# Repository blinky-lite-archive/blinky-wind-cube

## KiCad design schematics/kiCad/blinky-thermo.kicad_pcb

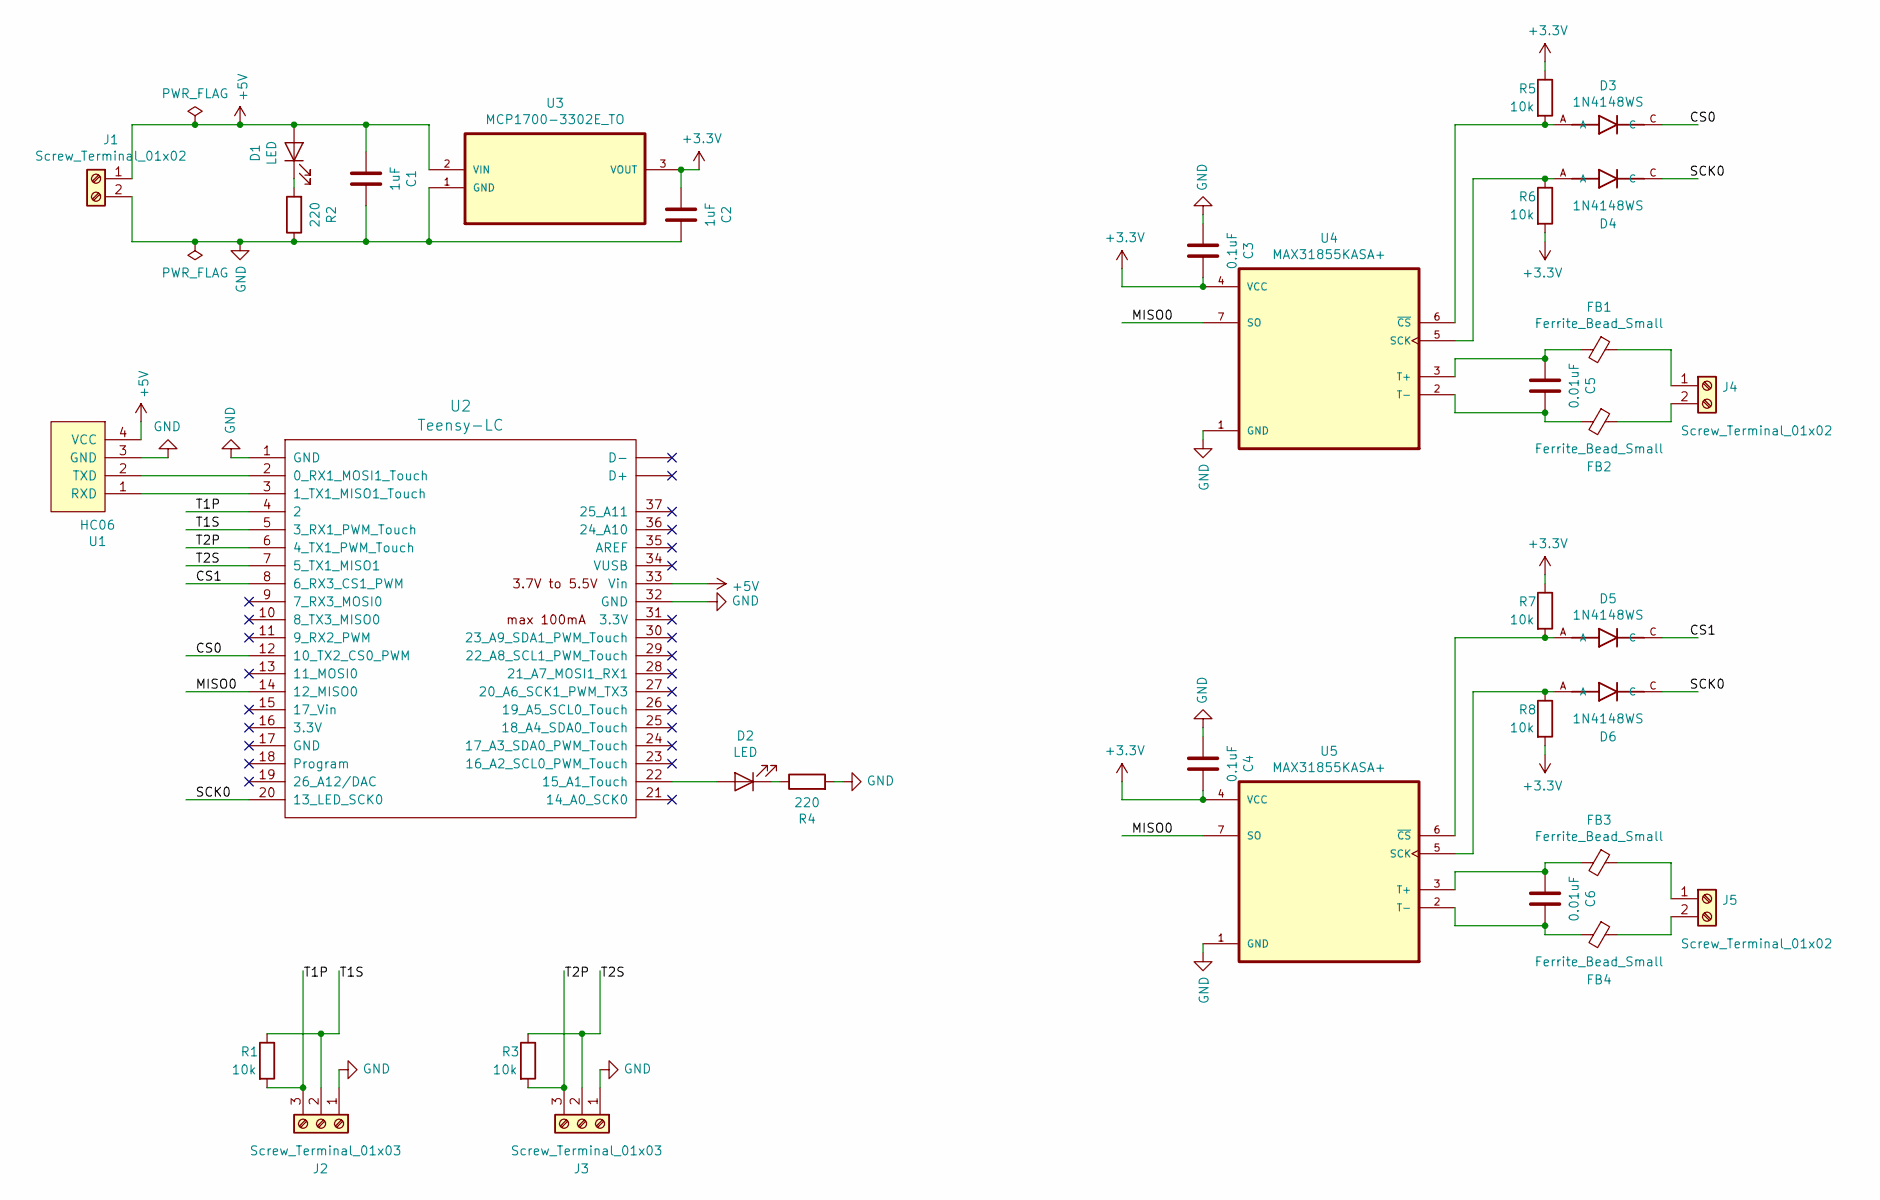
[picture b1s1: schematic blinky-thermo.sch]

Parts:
C1, C2: 1uF; C_1206_3216Metric_Pad1.42x1.75mm_HandSolder
C3, C4: 0.1uF; C_1206_3216Metric_Pad1.42x1.75mm_HandSolder
C5, C6: 0.01uF; C_1206_3216Metric_Pad1.42x1.75mm_HandSolder
D1, D2: LED; LED_D5.0mm
D3, D4, D5, D6: 1N4148WS; SODFL2512X100N
FB1, FB2, FB3, FB4: Ferrite_Bead_Small; L_1206_3216Metric_Pad1.42x1.75mm_HandSolder
J1, J4, J5: Screw_Terminal_01x02; TerminalBlock_bornier-2_P5.08mm
J2, J3: Screw_Terminal_01x03; TerminalBlock_bornier-3_P5.08mm
R1, R3, R5, R6, R7, R8: 10k; R_1206_3216Metric_Pad1.42x1.75mm_HandSolder
R2, R4: 220; R_1206_3216Metric_Pad1.42x1.75mm_HandSolder
U1: HC06
U2: Teensy-LC; Teensy30_31_32_LC
U3: MCP1700-3302E_TO; TO127P254X495-3; MPN MCP1700-3302E/TO
U4, U5: MAX31855KASA+; SOIC127P600X175-8N

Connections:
+3V3: C2.2, C3.1, C4.1, R5.1, R6.2, R7.1, R8.2, U3.3 (VOUT), U4.4 (VCC), U5.4 (VCC)
+5V: C1.2, D1.2 (A), J1.1, U1.4 (VCC), U2.33 (Vin), U3.2 (VIN)
/CS0: D3.C, U2.12 (10_TX2_CS0_PWM)
/CS1: D5.C, U2.8 (6_RX3_CS1_PWM)
/MISO0: U2.14 (12_MISO0), U4.7 (SO), U5.7 (SO)
/SCK0: D4.C, D6.C, U2.20 (13_LED_SCK0)
/T1P: J2.3, R1.2, U2.4 (2)
/T1S: J2.2, R1.1, U2.5 (3_RX1_PWM_Touch)
/T2P: J3.3, R3.2, U2.6 (4_TX1_PWM_Touch)
/T2S: J3.2, R3.1, U2.7 (5_TX1_MISO1)
GND: C1.1, C2.1, C3.2, C4.2, J1.2, J2.1, J3.1, R2.1, R4.2, U1.3 (GND), U2.1 (GND), U2.32 (GND), U3.1 (GND), U4.1 (GND), U5.1 (GND)
unnamed: C5.1, FB2.2, U4.2 (T-)
unnamed: C5.2, FB1.2, U4.3 (T+)
unnamed: C6.1, FB4.2, U5.2 (T-)
unnamed: C6.2, FB3.2, U5.3 (T+)
unnamed: D1.1 (K), R2.2
unnamed: D2.1 (K), R4.1
unnamed: D2.2 (A), U2.22 (15_A1_Touch)
unnamed: D3.A, R5.2, U4.6 (~CS)
unnamed: D4.A, R6.1, U4.5 (SCK)
unnamed: D5.A, R7.2, U5.6 (~CS)
unnamed: D6.A, R8.1, U5.5 (SCK)
unnamed: FB1.1, J4.1
unnamed: FB2.1, J4.2
unnamed: FB3.1, J5.1
unnamed: FB4.1, J5.2
unnamed: U1.1 (RXD), U2.3 (1_TX1_MISO1_Touch)
unnamed: U1.2 (TXD), U2.2 (0_RX1_MOSI1_Touch)

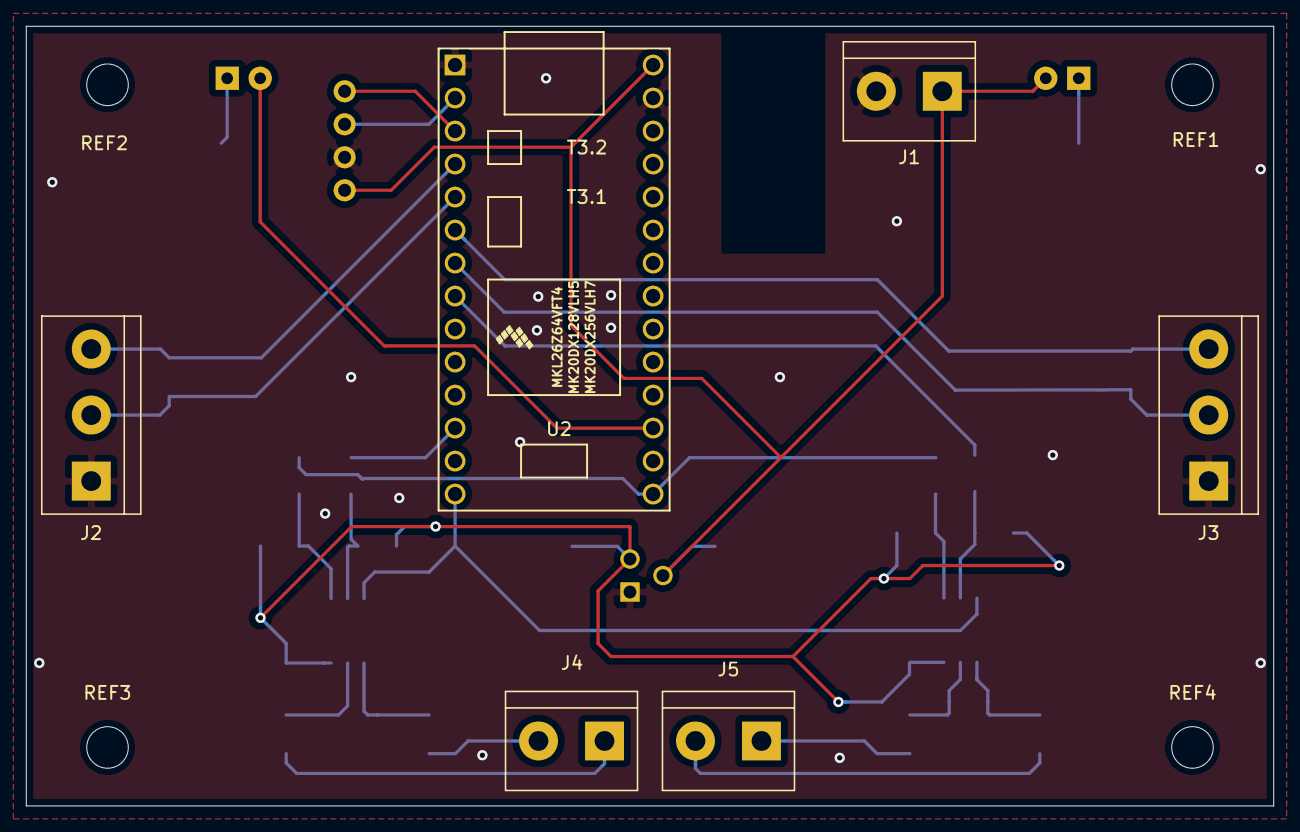
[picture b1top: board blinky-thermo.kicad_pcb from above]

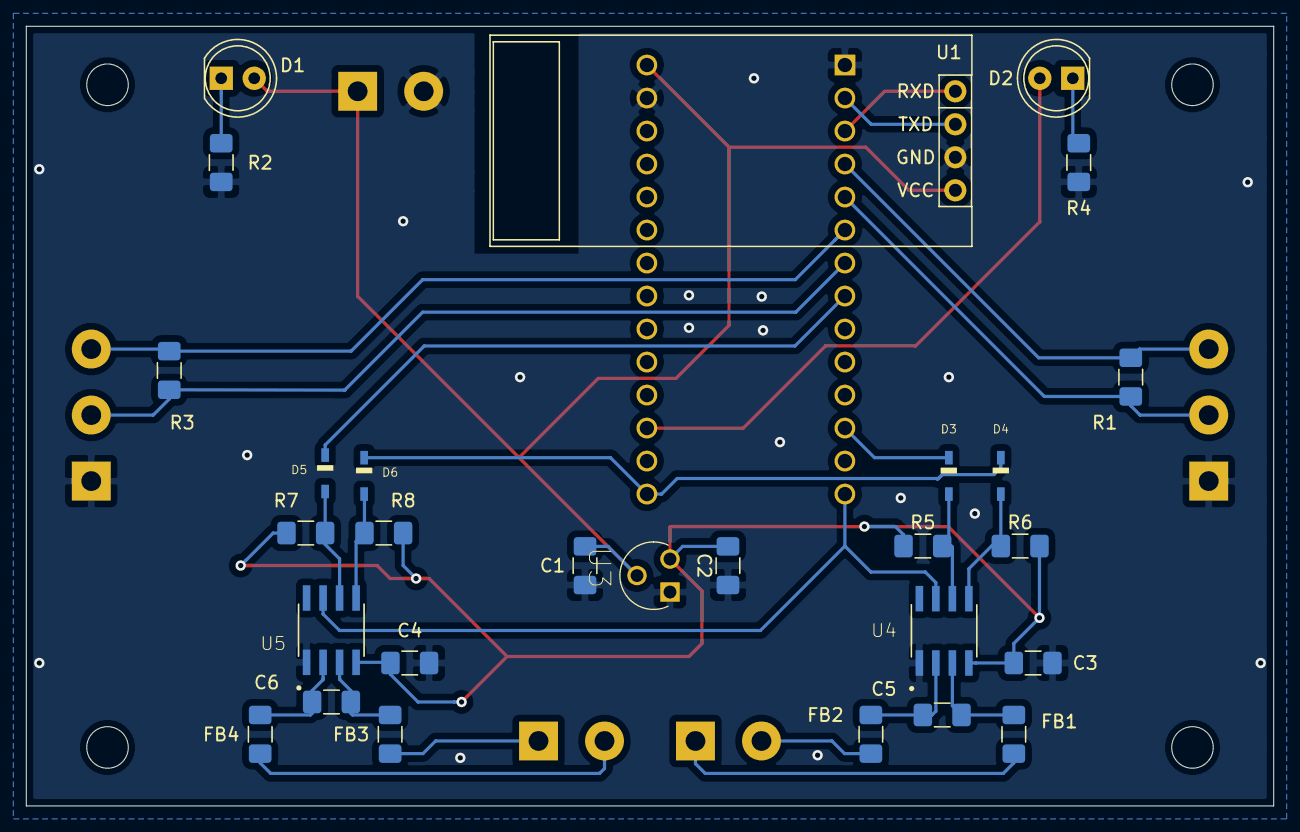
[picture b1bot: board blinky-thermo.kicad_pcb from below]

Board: 2 copper layers, 96.0 x 60.0 mm, 38 parts (28 on the bottom side), 28 nets.

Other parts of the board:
REF1, REF2, REF3, REF4: MountingHole_3.2mm_M3

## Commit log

2021-01-12 pcb designed
2021-02-01 working cube code
2021-03-29 cube code with checksum
2021-04-05 reading speed and direction
2021-04-05 changed to m/s
2021-04-05 updated baud rate
2021-04-05 added temp
2021-04-06 new pins for new box
2021-04-12 update hc06 setup
2021-06-11 with lora link
2021-06-24 added signal strength
2021-08-26 new windmill with new circuit
